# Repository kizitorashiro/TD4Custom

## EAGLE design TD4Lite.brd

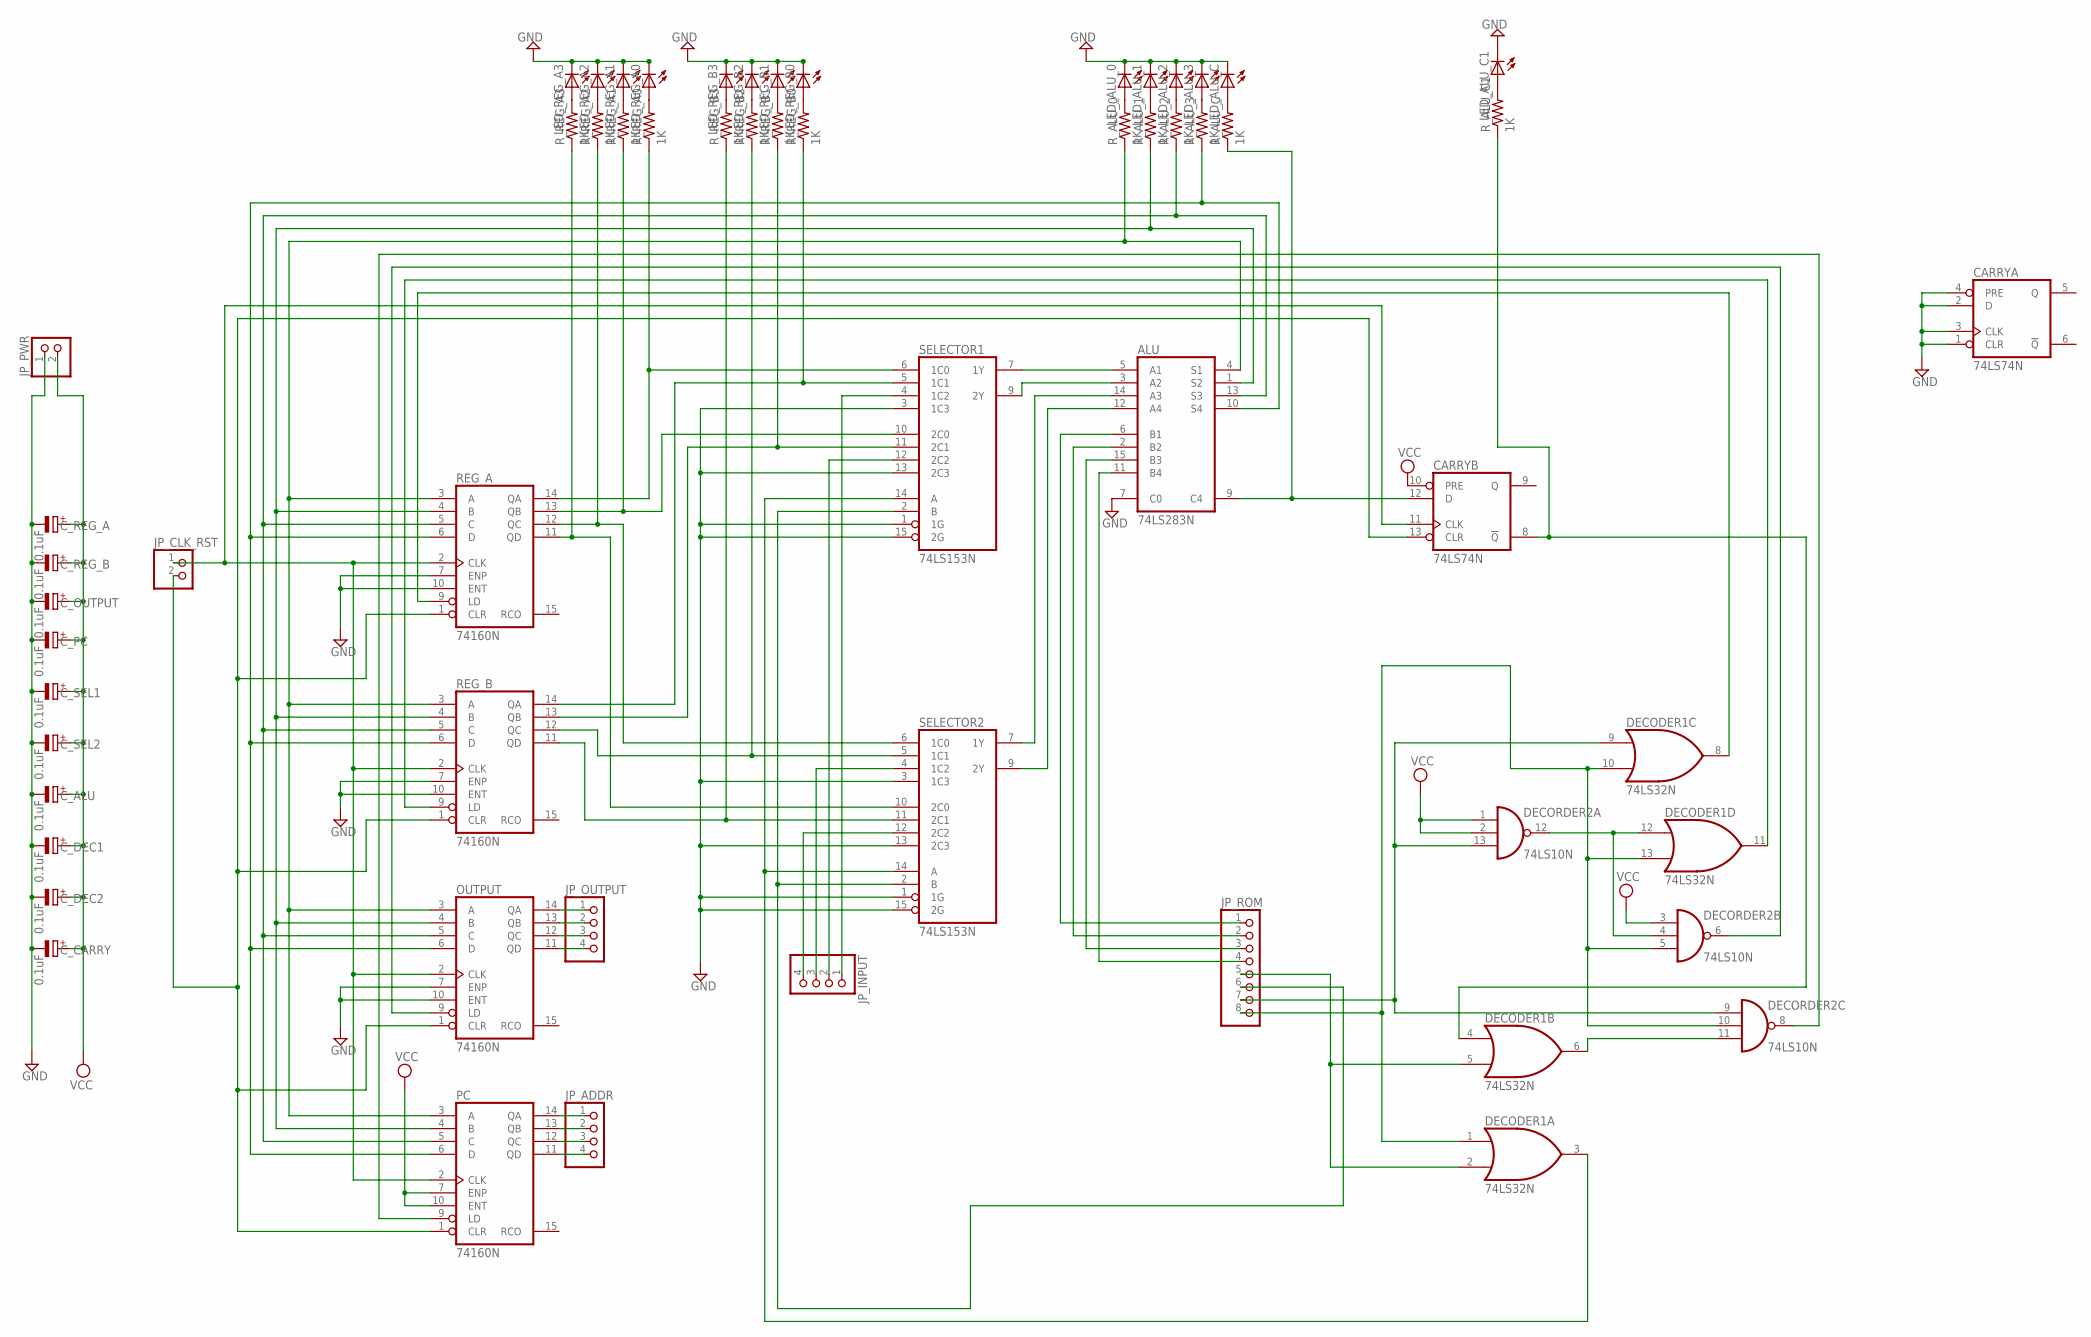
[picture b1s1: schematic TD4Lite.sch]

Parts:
ALU: 74LS283N; DIL16
CARRY: 74LS74N; DIL14
C_ALU: 0.1uF; E2-5
C_CARRY: 0.1uF; E2-5
C_DEC1, C_DEC2: 0.1uF; E2-5
C_OUTPUT: 0.1uF; E2-5
C_PC: 0.1uF; E2-5
C_REG_A: 0.1uF; E2-5
C_REG_B: 0.1uF; E2-5
C_SEL1, C_SEL2: 0.1uF; E2-5
DECODER1: 74LS32N; DIL14
DECORDER2: 74LS10N; DIL14
JP_ADDR: PINHD-1X4; 1X04
JP_CLK_RST: PINHD-1X2; 1X02
JP_INPUT: PINHD-1X4; 1X04
JP_OUTPUT: PINHD-1X4; 1X04
JP_PWR: PINHD-1X2; 1X02
JP_ROM: PINHD-1X8; 1X08
LED_ALU_0, LED_ALU_1, LED_ALU_2, LED_ALU_3: LED5MM
LED_ALU_C, LED_ALU_C1: LED5MM
LED_REG_A0, LED_REG_A1, LED_REG_A2, LED_REG_A3: LED5MM
LED_REG_B0, LED_REG_B1, LED_REG_B2, LED_REG_B3: LED5MM
OUTPUT: 74160N; DIL16
PC: 74160N; DIL16
REG_A: 74160N; DIL16
REG_B: 74160N; DIL16
R_ALU_0, R_ALU_1, R_ALU_2, R_ALU_3: 1K; 0204/7
R_ALU_C, R_ALU_C1: 1K; 0204/7
R_REG_A0, R_REG_A1, R_REG_A2, R_REG_A3: 1K; 0204/7
R_REG_B0, R_REG_B1, R_REG_B2, R_REG_B3: 1K; 0204/7
SELECTOR1, SELECTOR2: 74LS153N; DIL16

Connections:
CLK: CARRY.11 (CLK), JP_CLK_RST.1, OUTPUT.2 (CLK), PC.2 (CLK), REG_A.2 (CLK), REG_B.2 (CLK)
DATA_0: ALU.6 (B1), JP_ROM.1
DATA_1: ALU.2 (B2), JP_ROM.2
DATA_2: ALU.15 (B3), JP_ROM.3
DATA_3: ALU.11 (B4), JP_ROM.4
DATA_4: DECODER1.2 (I1), DECODER1.5 (I1), JP_ROM.5
DATA_5: JP_ROM.6, SELECTOR1.2 (B), SELECTOR2.2 (B)
DATA_6: DECODER1.9 (I0), DECORDER2.9 (I0), DECORDER2.13 (I2), JP_ROM.7
DATA_7: DECODER1.1 (I0), DECODER1.10 (I1), DECODER1.13 (I1), DECORDER2.5 (I2), DECORDER2.10 (I1), JP_ROM.8
GND: ALU.7 (C0), ALU.8 (GND), CARRY.1 (CLR), CARRY.2 (D), CARRY.3 (CLK), CARRY.4 (PRE), CARRY.7 (GND), C_ALU.-, C_CARRY.-, C_DEC1.-, C_DEC2.-, C_OUTPUT.-, C_PC.-, C_REG_A.-, C_REG_B.-, C_SEL1.-, C_SEL2.-, DECODER1.7 (GND), DECORDER2.7 (GND), JP_PWR.1, LED_ALU_0.K (C), LED_ALU_1.K (C), LED_ALU_2.K (C), LED_ALU_3.K (C), LED_ALU_C.K (C), LED_ALU_C1.K (C), LED_REG_A0.K (C), LED_REG_A1.K (C), LED_REG_A2.K (C), LED_REG_A3.K (C), LED_REG_B0.K (C), LED_REG_B1.K (C), LED_REG_B2.K (C), LED_REG_B3.K (C), OUTPUT.7 (ENP), OUTPUT.8 (GND), OUTPUT.10 (ENT), PC.8 (GND), REG_A.7 (ENP), REG_A.8 (GND), REG_A.10 (ENT), REG_B.7 (ENP), REG_B.8 (GND), REG_B.10 (ENT), SELECTOR1.1 (1G), SELECTOR1.3 (1C3), SELECTOR1.8 (GND), SELECTOR1.13 (2C3), SELECTOR1.15 (2G), SELECTOR2.1 (1G), SELECTOR2.3 (1C3), SELECTOR2.8 (GND), SELECTOR2.13 (2C3), SELECTOR2.15 (2G)
unnamed: LED_ALU_0.A, R_ALU_0.2
unnamed: LED_ALU_1.A, R_ALU_1.2
unnamed: LED_ALU_2.A, R_ALU_2.2
unnamed: LED_ALU_3.A, R_ALU_3.2
unnamed: ALU.4 (S1), OUTPUT.3 (A), PC.3 (A), REG_A.3 (A), REG_B.3 (A), R_ALU_0.1
unnamed: LED_ALU_C.A, R_ALU_C.2
unnamed: ALU.1 (S2), OUTPUT.4 (B), PC.4 (B), REG_A.4 (B), REG_B.4 (B), R_ALU_1.1
unnamed: ALU.13 (S3), OUTPUT.5 (C), PC.5 (C), REG_A.5 (C), REG_B.5 (C), R_ALU_2.1
unnamed: ALU.10 (S4), OUTPUT.6 (D), PC.6 (D), REG_A.6 (D), REG_B.6 (D), R_ALU_3.1
unnamed: LED_ALU_C1.A, R_ALU_C1.2
unnamed: CARRY.8 (!Q), DECODER1.4 (I0), R_ALU_C1.1
unnamed: LED_REG_A3.A, R_REG_A3.2
unnamed: LED_REG_A2.A, R_REG_A2.2
unnamed: LED_REG_A1.A, R_REG_A1.2
unnamed: LED_REG_A0.A, R_REG_A0.2
unnamed: LED_REG_B3.A, R_REG_B3.2
unnamed: LED_REG_B2.A, R_REG_B2.2
unnamed: LED_REG_B1.A, R_REG_B1.2
unnamed: LED_REG_B0.A, R_REG_B0.2
unnamed: JP_INPUT.1, SELECTOR1.4 (1C2)
unnamed: JP_INPUT.2, SELECTOR1.12 (2C2)
unnamed: JP_INPUT.3, SELECTOR2.4 (1C2)
unnamed: JP_INPUT.4, SELECTOR2.12 (2C2)
unnamed: ALU.5 (A1), SELECTOR1.7 (1Y)
unnamed: ALU.3 (A2), SELECTOR1.9 (2Y)
unnamed: ALU.14 (A3), SELECTOR2.7 (1Y)
unnamed: ALU.12 (A4), SELECTOR2.9 (2Y)
unnamed: JP_OUTPUT.4, OUTPUT.11 (QD)
unnamed: JP_OUTPUT.2, OUTPUT.13 (QB)
unnamed: JP_OUTPUT.1, OUTPUT.14 (QA)
unnamed: JP_OUTPUT.3, OUTPUT.12 (QC)
unnamed: JP_ADDR.1, PC.14 (QA)
unnamed: JP_ADDR.2, PC.13 (QB)
unnamed: JP_ADDR.3, PC.12 (QC)
unnamed: JP_ADDR.4, PC.11 (QD)
unnamed: ALU.9 (C4), CARRY.12 (D), R_ALU_C.1
unnamed: DECODER1.3 (O), SELECTOR1.14 (A), SELECTOR2.14 (A)
unnamed: DECODER1.8 (O), REG_A.9 (LD)
unnamed: DECODER1.12 (I0), DECORDER2.4 (I1), DECORDER2.12 (O)
unnamed: DECODER1.11 (O), REG_B.9 (LD)
unnamed: DECODER1.6 (O), DECORDER2.11 (I2)
unnamed: DECORDER2.6 (O), OUTPUT.9 (LD)
unnamed: DECORDER2.8 (O), PC.9 (LD)
REG_A0: REG_A.14 (QA), R_REG_A0.1, SELECTOR1.6 (1C0)
REG_A1: REG_A.13 (QB), R_REG_A1.1, SELECTOR1.10 (2C0)
REG_A2: REG_A.12 (QC), R_REG_A2.1, SELECTOR2.6 (1C0)
REG_A3: REG_A.11 (QD), R_REG_A3.1, SELECTOR2.10 (2C0)
REG_B0: REG_B.14 (QA), R_REG_B0.1, SELECTOR1.5 (1C1)
REG_B1: REG_B.13 (QB), R_REG_B1.1, SELECTOR1.11 (2C1)
REG_B2: REG_B.12 (QC), R_REG_B2.1, SELECTOR2.5 (1C1)
REG_B3: REG_B.11 (QD), R_REG_B3.1, SELECTOR2.11 (2C1)
RST: CARRY.13 (CLR), JP_CLK_RST.2, OUTPUT.1 (CLR), PC.1 (CLR), REG_A.1 (CLR), REG_B.1 (CLR)
VCC: ALU.16 (VCC), CARRY.10 (PRE), CARRY.14 (VCC), C_ALU.+, C_CARRY.+, C_DEC1.+, C_DEC2.+, C_OUTPUT.+, C_PC.+, C_REG_A.+, C_REG_B.+, C_SEL1.+, C_SEL2.+, DECODER1.14 (VCC), DECORDER2.1 (I0), DECORDER2.2 (I1), DECORDER2.3 (I0), DECORDER2.14 (VCC), JP_PWR.2, OUTPUT.16 (VCC), PC.7 (ENP), PC.10 (ENT), PC.16 (VCC), REG_A.16 (VCC), REG_B.16 (VCC), SELECTOR1.16 (VCC), SELECTOR2.16 (VCC)

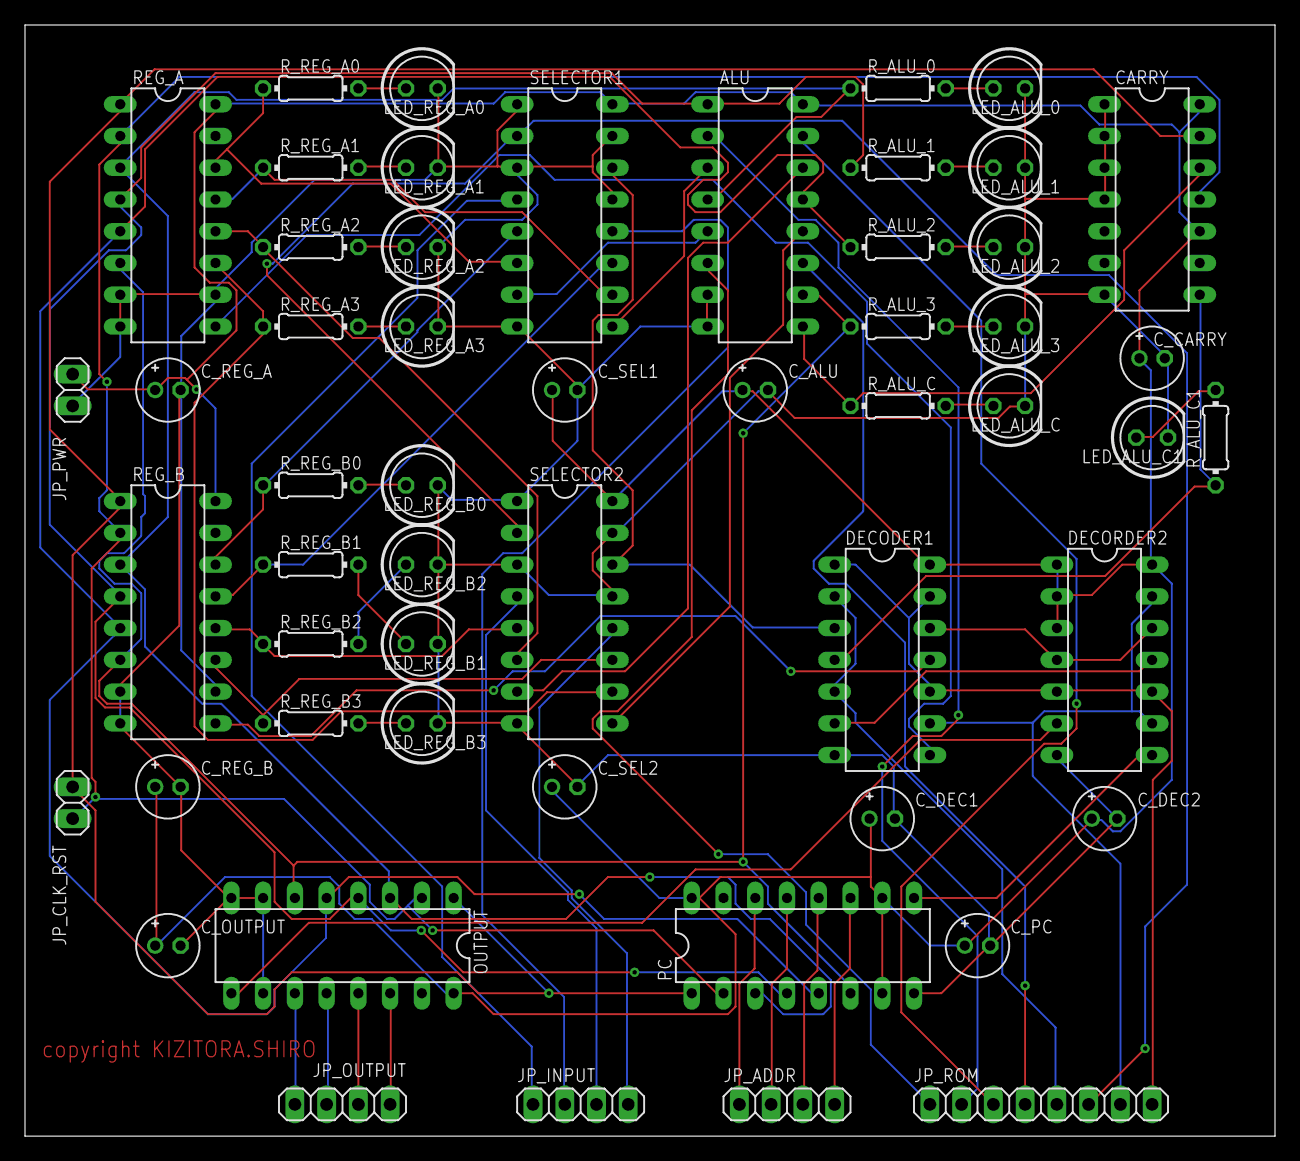
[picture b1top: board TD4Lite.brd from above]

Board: 2 copper layers, 100.0 x 88.9 mm, 54 parts (0 on the bottom side), 63 nets.

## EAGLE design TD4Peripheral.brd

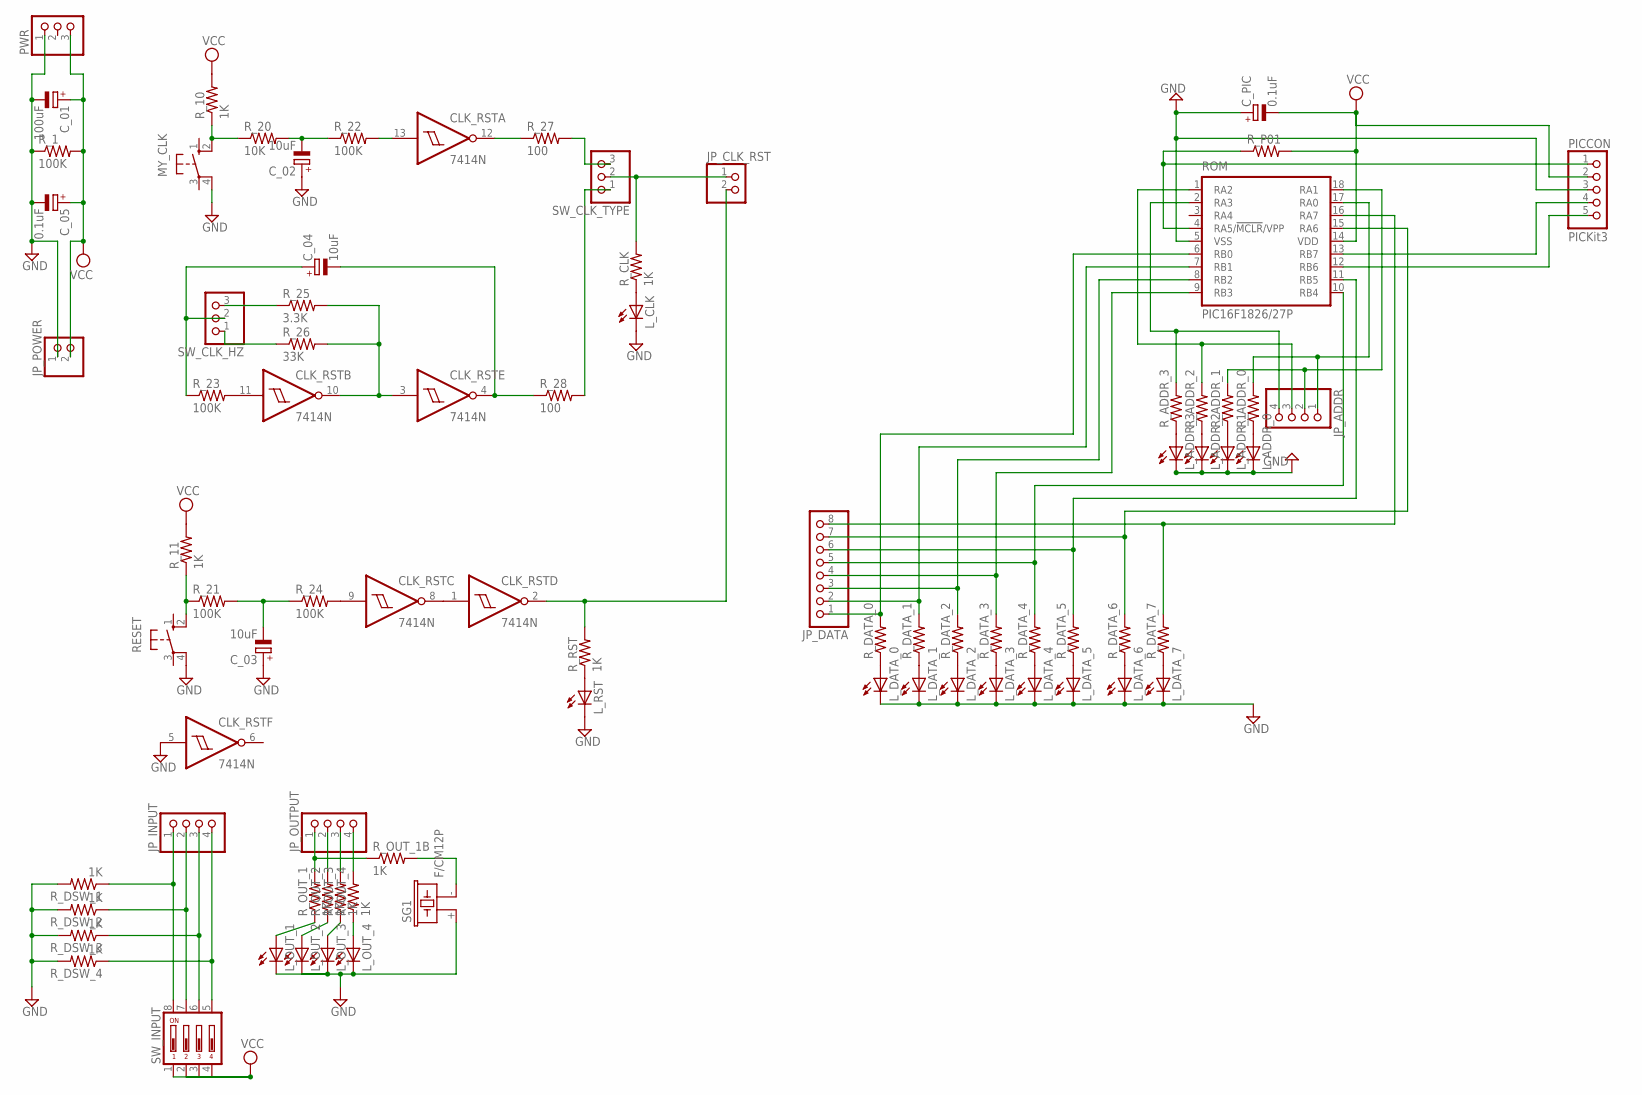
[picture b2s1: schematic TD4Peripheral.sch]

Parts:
CLK_RST: 7414N; DIL14
C_01: 100uF; E2-5
C_02, C_03, C_04: 10uF; E2-5
C_05: 0.1uF; E2-5
C_PIC: 0.1uF; E2-5
JP_ADDR: PINHD-1X4; 1X04
JP_CLK_RST: PINHD-1X2; 1X02
JP_DATA: PINHD-1X8; 1X08
JP_INPUT: PINHD-1X4; 1X04
JP_OUTPUT: PINHD-1X4; 1X04
JP_POWER: PINHD-1X2; 1X02
L_ADDR_0, L_ADDR_1, L_ADDR_2, L_ADDR_3: LED5MM
L_CLK: LED5MM
L_DATA_0, L_DATA_1, L_DATA_2, L_DATA_3, L_DATA_4, L_DATA_5, L_DATA_6, L_DATA_7: LED5MM
L_OUT_1, L_OUT_2, L_OUT_3, L_OUT_4: LED5MM
L_RST: LED5MM
MY_CLK: 10-XX; B3F-10XX
PICCON: PICKit3; 1X05
PWR: PINHD-1X3; 1X03
RESET: 10-XX; B3F-10XX
ROM: PIC16F1826/27P; DIL18
R_1, R_21, R_22, R_23, R_24: 100K; 0204/7
R_10, R_11: 1K; 0204/7
R_20: 10K; 0204/7
R_25: 3.3K; 0204/7
R_26: 33K; 0204/7
R_27, R_28: 100; 0204/7
R_ADDR_0, R_ADDR_1, R_ADDR_2, R_ADDR_3: R-US_0204/7; 0204/7
R_CLK: 1K; 0204/7
R_DATA_0, R_DATA_1, R_DATA_2, R_DATA_3, R_DATA_4, R_DATA_5, R_DATA_6, R_DATA_7: R-US_0204/7; 0204/7
R_DSW_1, R_DSW_2, R_DSW_3, R_DSW_4: 1K; 0204/7
R_OUT_1, R_OUT_1B, R_OUT_2, R_OUT_3, R_OUT_4: 1K; 0204/7
R_P01: R-US_0204/7; 0204/7
R_RST: 1K; 0204/7
SG1: F/CM12P
SW_CLK_HZ: PINHD-1X3; 1X03
SW_CLK_TYPE: PINHD-1X3; 1X03
SW_INPUT: DP04; DP-04

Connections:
ADDR_0: JP_ADDR.1, ROM.17 (RA0), R_ADDR_0.2
ADDR_1: JP_ADDR.2, ROM.18 (RA1), R_ADDR_1.2
ADDR_2: JP_ADDR.3, ROM.1 (RA2), R_ADDR_2.2
ADDR_3: JP_ADDR.4, ROM.2 (RA3), R_ADDR_3.2
DATA_0: JP_DATA.1, ROM.6 (RB0), R_DATA_0.2
DATA_1: JP_DATA.2, ROM.7 (RB1), R_DATA_1.2
DATA_2: JP_DATA.3, ROM.8 (RB2), R_DATA_2.2
DATA_3: JP_DATA.4, ROM.9 (RB3), R_DATA_3.2
DATA_4: JP_DATA.5, ROM.10 (RB4), R_DATA_4.2
DATA_5: JP_DATA.6, ROM.11 (RB5), R_DATA_5.2
DATA_6: JP_DATA.7, ROM.15 (RA6), R_DATA_6.2
DATA_7: JP_DATA.8, ROM.16 (RA7), R_DATA_7.2
GND: CLK_RST.5 (I), CLK_RST.7 (GND), C_01.-, C_02.+, C_03.+, C_05.-, C_PIC.+, JP_POWER.1, L_ADDR_0.K (C), L_ADDR_1.K (C), L_ADDR_2.K (C), L_ADDR_3.K (C), L_CLK.K (C), L_DATA_0.K (C), L_DATA_1.K (C), L_DATA_2.K (C), L_DATA_3.K (C), L_DATA_4.K (C), L_DATA_5.K (C), L_DATA_6.K (C), L_DATA_7.K (C), L_OUT_1.K (C), L_OUT_2.K (C), L_OUT_3.K (C), L_OUT_4.K (C), L_RST.K (C), MY_CLK.4 (P1), PICCON.3, PWR.1, RESET.4 (P1), ROM.5 (VSS), R_1.1, R_DSW_1.2, R_DSW_2.2, R_DSW_3.2, R_DSW_4.2, SG1.+ (1)
ICSPCLK: PICCON.5, ROM.12 (RB6)
ICSPDAT: PICCON.4, ROM.13 (RB7)
MCLR: PICCON.1, ROM.4 (RA5/!MCLR!/VPP), R_P01.1
unnamed: MY_CLK.2 (S1), R_10.1, R_20.1
unnamed: C_02.-, R_20.2, R_22.1
unnamed: CLK_RST.13 (I), R_22.2
unnamed: CLK_RST.12 (O), R_27.1
unnamed: R_27.2, SW_CLK_TYPE.3
unnamed: C_04.+, R_23.1, SW_CLK_HZ.2
unnamed: R_25.1, SW_CLK_HZ.3
unnamed: R_26.1, SW_CLK_HZ.1
unnamed: CLK_RST.11 (I), R_23.2
unnamed: CLK_RST.3 (I), CLK_RST.10 (O), R_25.2, R_26.2
unnamed: R_28.2, SW_CLK_TYPE.1
unnamed: CLK_RST.4 (O), C_04.-, R_28.1
unnamed: RESET.2 (S1), R_11.1, R_21.1
unnamed: C_03.-, R_21.2, R_24.1
unnamed: CLK_RST.9 (I), R_24.2
unnamed: CLK_RST.1 (I), CLK_RST.8 (O)
unnamed: CLK_RST.2 (O), JP_CLK_RST.2, R_RST.2
unnamed: JP_CLK_RST.1, R_CLK.2, SW_CLK_TYPE.2
unnamed: L_DATA_7.A, R_DATA_7.1
unnamed: L_DATA_6.A, R_DATA_6.1
unnamed: L_DATA_5.A, R_DATA_5.1
unnamed: L_DATA_4.A, R_DATA_4.1
unnamed: L_DATA_3.A, R_DATA_3.1
unnamed: L_DATA_2.A, R_DATA_2.1
unnamed: L_DATA_1.A, R_DATA_1.1
unnamed: L_ADDR_0.A, R_ADDR_0.1
unnamed: L_ADDR_1.A, R_ADDR_1.1
unnamed: L_ADDR_2.A, R_ADDR_2.1
unnamed: L_CLK.A, R_CLK.1
unnamed: L_RST.A, R_RST.1
unnamed: L_ADDR_3.A, R_ADDR_3.1
unnamed: L_DATA_0.A, R_DATA_0.1
N_OUT1: JP_OUTPUT.1, R_OUT_1.2, R_OUT_1B.1
N_OUT2: JP_OUTPUT.2, R_OUT_2.2
N_OUT3: JP_OUTPUT.3, R_OUT_3.2
N_OUT4: JP_OUTPUT.4, R_OUT_4.2
N_OUT_1: L_OUT_1.A, R_OUT_1.1
N_OUT_1B: R_OUT_1B.2, SG1.- (2)
N_OUT_2: L_OUT_2.A, R_OUT_2.1
N_OUT_3: L_OUT_3.A, R_OUT_3.1
N_OUT_4: L_OUT_4.A, R_OUT_4.1
N_SW1: JP_INPUT.1, R_DSW_1.1, SW_INPUT.8
N_SW2: JP_INPUT.2, R_DSW_2.1, SW_INPUT.7
N_SW3: JP_INPUT.3, R_DSW_3.1, SW_INPUT.6
N_SW4: JP_INPUT.4, R_DSW_4.1, SW_INPUT.5
VCC: CLK_RST.14 (VCC), C_01.+, C_05.+, C_PIC.-, JP_POWER.2, PICCON.2, PWR.3, ROM.14 (VDD), R_1.2, R_10.2, R_11.2, R_P01.2, SW_INPUT.1, SW_INPUT.2, SW_INPUT.3, SW_INPUT.4

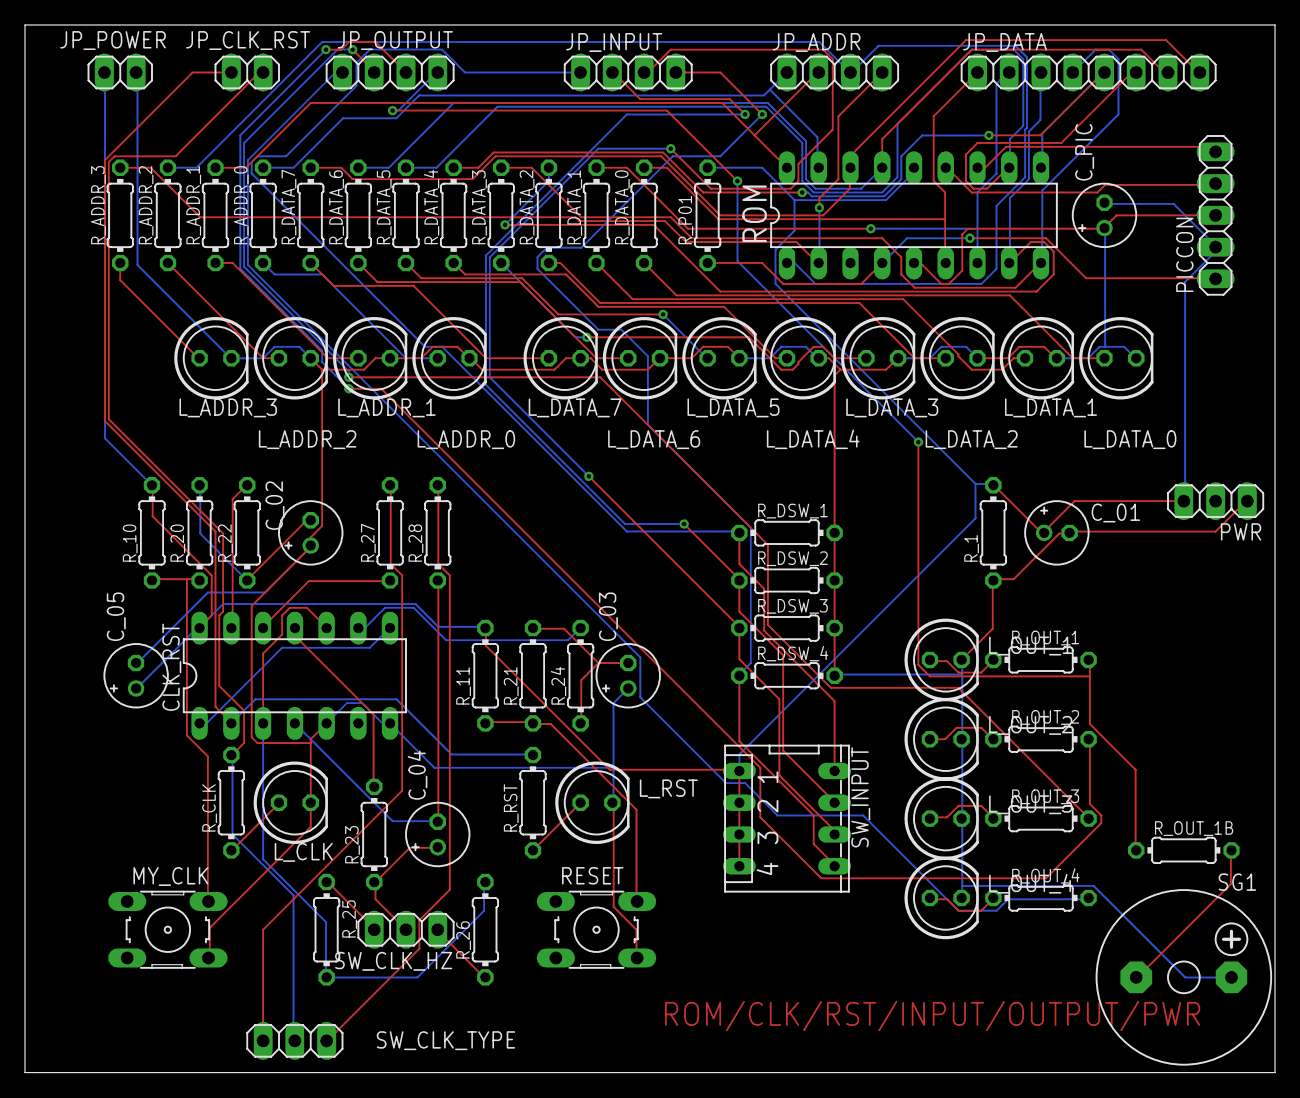
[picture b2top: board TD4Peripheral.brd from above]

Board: 2 copper layers, 100.0 x 83.8 mm, 76 parts (0 on the bottom side), 62 nets.

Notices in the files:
TD4Lite.brd:
copyright KIZITORA.SHIRO
